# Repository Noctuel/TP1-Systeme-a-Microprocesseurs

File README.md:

# Domingo Dorian - SIMOES Raphael - TP1-Systeme-a-Microprocesseurs
# 1.1 Création de la structure du projet
6. Activez l’USART2 en mode Asynchrone. Gardez les paramètres par défaut, et notez le baud rate
=> baud rate 115200 Bits/s

# 1.2 Le microcontrôleur sous KiCAD
13. Pourquoi PB9 est relié à la masse ?
=>Cela permet de choisir le boot ici relier à la masse cela permet de boot sur la flash.
14. Quel est le rôle de L1, C5 et C7 ?
=>Il s'agit d'un filtre de la tension d'alimentation pour obtenir une tension d'alimentation pour l'ADC car ce composant est plus sensible
=> Il  y a deux capacité la petite filtre les petites variations et la grande les grandes variation
=> L'inductance est utiliser à la place d'une résistance pour éviter une chute de tension.

# 1.3 Le reste du schéma
3. Quelle page de la datasheet indique les valeurs des condensateurs ?
=> page 3 "Recommended Operating Conditions"
5. Quelle page de la datasheet nous indique les valeurs de condensateurs ?
=> Digital Pin Capacitance page 6
6. Quel est le rôle de la broche CS ?
=>C'est le Chip Select actif à l'état bas qui permet d'activer/choisir le composant
7. Quel est le rôle de la broche LDAC ?
=>Il sert à transférer le registre d'entré à celui de sortie si il est à 0. On peut le piloter pour si on veux synchroniser plusieur DAC
8. Pourquoi le signal MISO n’est pas utilisé ?
=> Car le DAC ne répond pas au µp
10. Où trouve-t-on les indications du pinout du connecteur SWD ?
On les trouve dans la datasheet du stlink3set il s'agit d'une recopie du connecteur STDC14 c'est à dire le connecteur JTAG qui permet de reprogrammer le µp avec le protocole SWD

# 1.4 Affectation des empreintes
3. Que signifie 0805 ? 0603 ? 1206 ?
=> il s'agit des taille des composant (largeur / longueur)
4. Que signifie LQFP ? SOT-223 ? SOIC ? Ne vous contentez pas de donner le sigle,j’attends une petite description (vous pouvez copier-coller depuis wikipedia, mais lisez avant quand même))
=> LQFP : Low Profile Quad Flat Package
En électronique, Quad Flat Package (QFP) est un type de boîtier de circuit intégré destiné à être directement soudé sur circuit imprimé. Ce boîtier est normalisé suivant la JEDEC1
Le boîtier rectangulaire (en plastique ou en céramique) est doté de broches de connexion sur ses 4 côtés (jusqu'à 200 broches). Les broches sont généralement espacées de 0,4 à 1 mm, et sont extérieures au boîtier contrairement aux QFN.
=> SOT-223 : Il s'agit d'un réguleur de tension LDO
=> small outline integrated circuit : Circuit intégré en boîtier à dimension réduite présentant des connexions en aile de mouette sur deux rangées.

# 3.1 Activation des LL drivers
2. Regardez les fichiers générés. Quelles sont les différences ?
=> En paramètrant avec LL on utilise les fonctions du meme nom qui sont moins lourd par exemple stm32l0xx.ll.usart.c fais 400 ligne contre 4000 pour sont équivalent en HAL
=> On doit utiliser ces fonctions car notre processeur n'aura pas assez de mémoire

4. Que signifie __STATIC_INLINE ?
=>Inline veut dire que la fonction n'est pas une réel fonction mais que l'on va recopier son code à l'endroit ou on la appeler
5. Et pourquoi y a-t-il du code dans un .h alors que Môssieur Fiack vous a expres-sément demandé de pas le faire ? (Les deux questions sont peut-être liés, va savoir)
=> C'est justement a cause de Inline que l'on écrit dans le header

# 3.2 LED simple
2. On compte de 0 à 255 on a donc une fréquence de 32 000 000 /256 = 125 000 Hz. On doit donc avoir un prescaler de 125-1 (on compte de 0)
8. Le fonctionnement a été validé par l'enseignant.

# 3.3 LED avec timer
3. On peut laisser PSC à 0 et seuleument mettre ARR à 32 000-1(on compte de 0) pour obtenir notre fréquence de 1 kHz (32 000 000/32 000=1 000 Hz).
6. Dans"stm32l0xx_it.c"
7. Il manque la fonction qui retire l'interuption
8. On reste bloqué indéfinement dans l'interuption
9. Appeler immidiatement la fonction du timer qui retire le flag dans notre fonction d'interruption du Timer
11. Le fonctionnement a été validé par l'enseignant.

# 3.4 UART, un simple echo

5. Il manque & à ch pour passer l'adresse de ch

6. Le fonctionnement a été validé par l'enseignant.

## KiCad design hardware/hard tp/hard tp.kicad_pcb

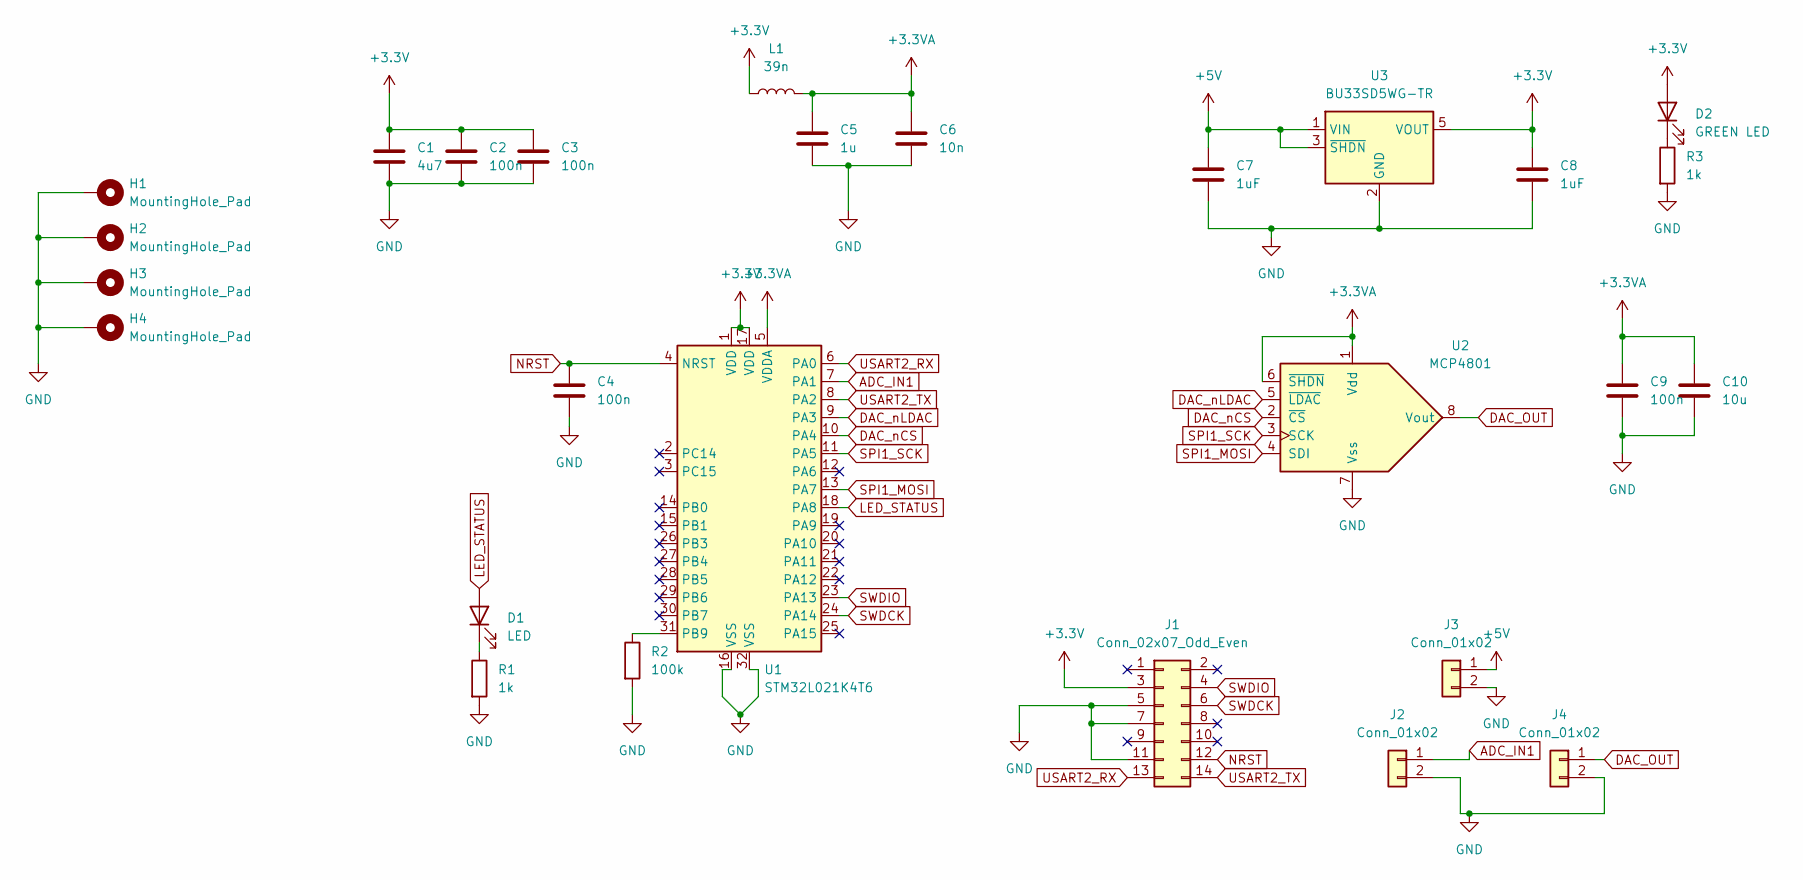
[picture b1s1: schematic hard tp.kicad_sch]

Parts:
C1: 4u7; C_0805_2012Metric_Pad1.18x1.45mm_HandSolder
C2, C3, C4, C9: 100n; C_0805_2012Metric_Pad1.18x1.45mm_HandSolder
C5: 1u; C_0805_2012Metric_Pad1.18x1.45mm_HandSolder
C6: 10n; C_0805_2012Metric_Pad1.18x1.45mm_HandSolder
C7, C8: 1uF; C_0805_2012Metric
C10: 10u; C_0805_2012Metric
D1: LED; LED_0603_1608Metric_Pad1.05x0.95mm_HandSolder
D2: GREEN LED; LED_0603_1608Metric_Pad1.05x0.95mm_HandSolder
H1, H2, H3, H4: MountingHole_Pad; MountingHole_3.2mm_M3_Pad
J1: Conn_02x07_Odd_Even; PinHeader_2x07_P1.27mm_Vertical_SMD
J2, J3, J4: Conn_01x02; JST_XH_B2B-XH-A_1x02_P2.50mm_Vertical
L1: 39n; L_0805_2012Metric_Pad1.05x1.20mm_HandSolder
R1, R3: 1k; R_0805_2012Metric_Pad1.20x1.40mm_HandSolder
R2: 100k; R_0805_2012Metric_Pad1.20x1.40mm_HandSolder
U1: STM32L021K4T6; LQFP-32_7x7mm_P0.8mm
U2: MCP4801; SOIC-8_3.9x4.9mm_P1.27mm
U3: BU33SD5WG-TR; SOT-23-5

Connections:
+3.3V: C1.1, C2.1, C3.1, C8.1, D2.2 (A), J1.3, L1.1, U1.1 (VDD), U1.17 (VDD), U3.5 (VOUT)
+3.3VA: C5.1, C6.1, C9.1, C10.1, L1.2, U1.5 (VDDA), U2.1 (Vdd), U2.6 (~SHDN)
+5V: C7.1, J3.1, U3.1 (VIN), U3.3 (~SHDN)
ADC_IN1: J2.1, U1.7 (PA1)
DAC_OUT: J4.1, U2.8 (Vout)
DAC_nCS: U1.10 (PA4), U2.2 (~CS)
DAC_nLDAC: U1.9 (PA3), U2.5 (~LDAC)
GND: C1.2, C2.2, C3.2, C4.2, C5.2, C6.2, C7.2, C8.2, C9.2, C10.2, H1.1, H2.1, H3.1, H4.1, J1.5, J1.7, J1.11, J2.2, J3.2, J4.2, R1.2, R2.2, R3.2, U1.16 (VSS), U1.32 (VSS), U2.7 (Vss), U3.2 (GND)
LED_STATUS: D1.2 (A), U1.18 (PA8)
NRST: C4.1, J1.12, U1.4 (NRST)
unnamed: D1.1 (K), R1.1
unnamed: D2.1 (K), R3.1
unnamed: R2.1, U1.31 (PB9)
SPI1_MOSI: U1.13 (PA7), U2.4 (SDI)
SPI1_SCK: U1.11 (PA5), U2.3 (SCK)
SWDCK: J1.6, U1.24 (PA14)
SWDIO: J1.4, U1.23 (PA13)
USART2_RX: J1.13, U1.6 (PA0)
USART2_TX: J1.14, U1.8 (PA2)

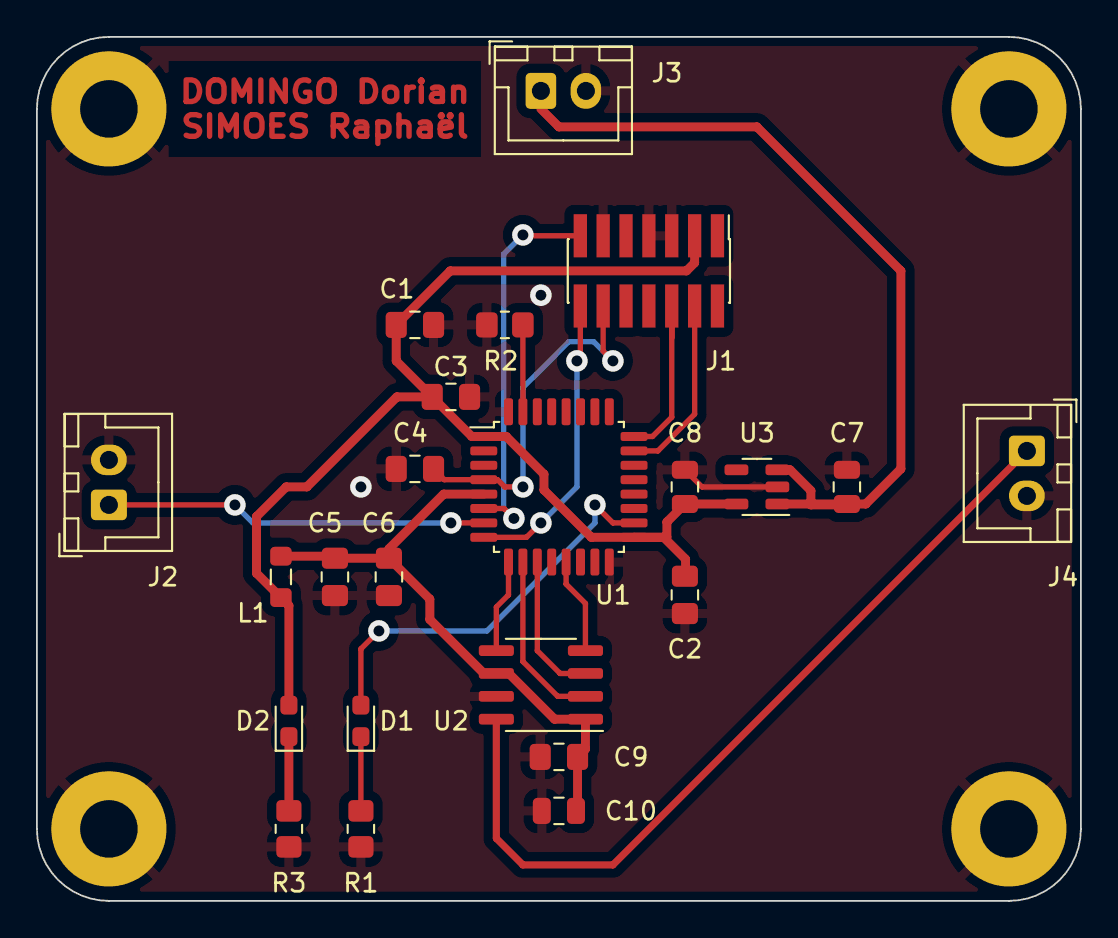
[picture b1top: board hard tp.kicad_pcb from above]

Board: 2 copper layers, 58.0 x 48.0 mm, 27 parts (0 on the bottom side), 19 nets.

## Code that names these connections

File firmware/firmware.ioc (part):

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Mcu.Name=STM32L021K4Tx
Mcu.Package=LQFP32
Mcu.UserName=STM32L021K4Tx
PA0-CK_IN.Mode=Asynchronous
PA0-CK_IN.Signal=USART2_RX
PA1.Mode=IN1
PA1.Signal=ADC_IN1
PA13.Mode=Serial_Wire
PA13.Signal=SYS_SWDIO
PA14.Mode=Serial_Wire
PA14.Signal=SYS_SWCLK
PA2.Mode=Asynchronous
PA2.Signal=USART2_TX
PA3.GPIOParameters=GPIO_Label
PA3.GPIO_Label=DAC_nLDAC
PA3.Signal=GPIO_Output
PA4.GPIOParameters=GPIO_Label
PA4.GPIO_Label=DAC_nCS
PA4.Signal=GPIO_Output
PA5.Mode=TX_Only_Simplex_Unidirect_Master
PA5.Signal=SPI1_SCK
PA7.Mode=TX_Only_Simplex_Unidirect_Master
PA7.Signal=SPI1_MOSI
PA8.Signal=S_TIM2_CH1
RCC.HSE_VALUE=8000000
RCC.SYSCLKFreq_VALUE=32000000
RCC.SYSCLKSource=RCC_SYSCLKSOURCE_PLLCLK
board=custom

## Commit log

2023-02-15 Create hardware
2023-02-15 add pdf
2023-02-15 add baudrate
2023-02-15 add firmware
2023-02-15 modif final séance 1
2023-02-16 readme change
2023-02-16 readme
2023-03-08 firmware update
2023-03-10 firmware change
